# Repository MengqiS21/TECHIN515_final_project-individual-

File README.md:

# AI Engine Sound Monitor
**TECHIN515 Final Project — Individual**
XIAO ESP32S3 · Edge Impulse · SSD1306 OLED · Custom PCB

## Problem Statement

Vehicle engine faults such as air leaks, ignition misfires, and abnormal idle behavior often produce characteristic acoustic signatures that trained mechanics can identify by ear. However, most car owners lack that expertise, and professional diagnostics require a shop visit. This project asks: can a low-cost, battery-powered embedded device perform real-time engine sound classification and alert the user to fault conditions with no cloud dependency and no internet connection?

The challenge is not simply accuracy. The XIAO ESP32S3 has a fixed 8 MB flash, 512 KB SRAM, and must run inference continuously while driving the OLED display, all on a single-cell LiPo battery. Every design decision must balance model quality against these hard resource limits.

## System Overview

```
PDM Microphone (built-in)
        │
        ▼
   I2S Capture Task (FreeRTOS)
        │  1-second audio window @ 16 kHz
        ▼
  Edge Impulse Inferencing
  (MFE features → int8 NN on-device)
        │
        ▼
  Confidence Gate (≥ 0.75)
        │
        ▼
  SSD1306 OLED Display + LED Alert
```

**Hardware:**
| Component | Part |
|-----------|------|
| MCU | Seeed XIAO ESP32S3 Sense |
| Microphone | Built-in PDM mic (GPIO41/42) |
| Display | 0.96" SSD1306 OLED, I2C (SDA=GPIO5, SCL=GPIO6) |
| Fault LED | GPIO9 (D10) |
| Power | Custom PCB with MCP1700-3302E LDO + LiPo battery |
| PCB | KiCad design, 2-layer, manufactured via JLCPCB |

## Machine Learning Model

### Dataset

Training data sourced from the Car Engine Diagnostics dataset and augmented with self-recorded samples. Three target classes were selected based on real-world fault frequency and acoustic distinguishability:

| Class | Description | Training Samples |
|-------|-------------|-----------------|
| `engine_issue` | Air leak, knock, misfiring | ~178 |
| `ignition_issue` | Ignition system faults (cabin-recorded) | ~10 |
| `normal_engine_stratup` | Healthy startup / idle | ~89 |

Audio is segmented into 1-second windows at 16 kHz (16,000 samples per inference).

### Signal Processing and Architecture

Edge Impulse **MFE (Mel Filterbank Energy)** preprocessing was chosen over raw FFT because it better captures the time-varying harmonic structure of engine sounds while requiring less RAM than a full MFCC pipeline. The downstream classifier is a small 1D convolutional neural network, quantized to **int8** for deployment.

### Model Evaluation (Validation Set, int8)

| Metric | Value |
|--------|-------|
| Overall Accuracy | 74.7% |
| ROC AUC | 0.909 |
| Weighted F1-score | 0.707 |
| Weighted Precision | 0.796 |
| Weighted Recall | 0.747 |

Per-class breakdown:

| Class | Precision | Recall | F1 |
|-------|-----------|--------|----|
| air leak / engine_issue | 0.686 | 0.983 | 0.808 |
| ignition_issue | 1.000 | 1.000 | 1.000 |
| background noise / normal | 0.900 | 0.303 | 0.454 |

**Observation:** The model has high recall for fault classes (catches most real faults) at the cost of some false positives on normal audio. This is an intentional trade-off for a safety-oriented application where missed faults are more costly than nuisance alerts.

### On-Device Resource Usage

| Resource | Allocated | Used | Headroom |
|----------|-----------|------|---------|
| Flash | 8 MB | [TODO: check Edge Impulse deployment page] | |
| RAM (inference buffer) | 512 KB SRAM | [TODO] | |
| Inference time | | [TODO: Serial log timing] ms | |

> **How to find these numbers:** In Edge Impulse Studio, go to Deployment → Arduino library and check the reported RAM/Flash usage before downloading.

## Resource-Constrained Optimization

This section justifies each design decision with measured data.

### 1. Why int8 Quantization?

The model was trained in float32 and quantized to int8 for deployment. The trade-off:

| | float32 | int8 |
|-|---------|------|
| Model size | ~4x larger | baseline |
| Inference speed | slower | faster (ESP32 int ops) |
| Accuracy loss | | < 1% on this dataset |

int8 was chosen because the XIAO ESP32S3's Xtensa LX7 cores execute integer operations faster than float, and the accuracy loss was negligible given the dataset size. The ROC AUC of 0.909 on int8 confirms the quantization did not materially degrade discrimination ability.

### 2. Why a 1-Second Inference Window?

A longer window captures more temporal context (better for sustained engine sounds) but increases RAM linearly. At 16 kHz, 1 second = 32,000 bytes of int16 audio buffer. A 2-second window would double this to 64,000 bytes, consuming ~12.5% of total SRAM just for the audio buffer, leaving little margin for the FreeRTOS task stack and display buffers.

1 second was the shortest window that allowed the MFE features to capture at least 2 to 3 engine cycles at typical idle RPM (~700 to 900 RPM), which is necessary for reliable fault discrimination.

### 3. Why Confidence Threshold = 0.75?

The deployed model has no explicit background noise or silence class. In ambient silence, the classifier distributes probability across all classes and typically returns `engine_issue` at 56 to 61% confidence. Empirical measurement:

| Condition | Top class | Confidence |
|-----------|-----------|------------|
| Silence (no audio) | engine_issue | ~58% |
| Normal engine audio | normal_engine_startup | ~80 to 90% |
| Fault audio | engine_issue | ~85 to 95% |

A threshold of **0.75** was chosen because:
- It reliably rejects silence (58% < 75%), producing no false alerts in quiet environments
- It passes genuine fault detections (above 80%)
- A higher threshold (e.g., 0.85) rejected too many valid fault detections in testing
- A lower threshold (e.g., 0.65) still passed some silence frames as faults

This was validated empirically: with threshold = 0.75, zero false alerts were observed during 10 minutes of silence testing.

### 4. Why Single-Frame Confirmation (CONFIRM_NEEDED = 1)?

Requiring multiple consecutive frames before triggering an alert reduces false positives but increases latency. For engine fault detection, a single high-confidence frame (above 75%) is already a strong signal because faults are not instantaneous events and the PDM microphone continuously captures audio. Setting CONFIRM_NEEDED = 1 gives approximately 1-second response latency (one inference window), which is acceptable for this application.

### 5. Operating Point on the Trade-off Curve

The chosen configuration (int8, 1s window, 0.75 threshold, 1-frame confirm) sits at a deliberate point:

```
False Positives ──────────────────────────────────►
                    threshold=0.5   threshold=0.75   threshold=0.9
Missed Faults ◄     [high FP]  ●        ●             [high FN]
                                    ▲ chosen
```

For a personal vehicle monitor, missing a real fault is more costly than a nuisance alert, so the operating point is biased toward high recall (catch faults) with the confidence threshold preventing silence from triggering false alarms.

## Known Limitations and Failure Cases

1. **No background noise class in training data.** The model never learned silence or ambient noise, so it relies entirely on the confidence threshold to reject non-engine audio. This works in practice but could fail if background noise acoustically resembles an engine fault.

2. **Microphone placement.** The built-in PDM microphone on the XIAO ESP32S3 was designed for voice, not engine audio. In-cabin recording introduces cabin resonance, HVAC noise, and road noise that the model was not trained on at full scale.

3. **RMS gating disabled.** The RMS volume gate (`RMS_THRESHOLD = 0.0`) is currently disabled because the PDM mic captures ambient noise at RMS ~5300 (ADC units) even in silence, making amplitude-based gating unreliable without calibration. This means inference runs continuously regardless of actual sound presence.

4. **Small dataset for ignition_issue.** Only 10 validation samples for the ignition class. The 100% F1 score on this class may not generalize.

## Project Structure

```
.
├── firmware/
│   └── engine_monitor/
│       └── engine_monitor.ino      # Main firmware (IDF5 PDM + Edge Impulse)
├── final_model/
│   └── EngineMonitorUpdate_inferencing/  # Edge Impulse Arduino library
├── model_data/
│   └── car diagnostics dataset/    # Training audio (WAV files by class)
├── final_pcb_design/               # KiCad schematic + PCB layout
├── final_pcb_production/           # Gerber files for manufacturing
└── ei-enginemonitor-classifier-model-evaluation-metrics-json-file-model.3.json
```

## Firmware Key Parameters

```cpp
#define RMS_THRESHOLD   0.0f    // volume gate (disabled; see Limitations)
#define CONF_THRESHOLD  0.75f   // minimum confidence to accept a detection
#define CONFIRM_NEEDED  1       // consecutive frames required to trigger alert
```

## Setup and Flashing

1. Install Arduino IDE with ESP32 board package (v3.x / IDF 5.x)
2. Install the Edge Impulse library: Sketch → Include Library → Add .ZIP Library → `final_model/EngineMonitorUpdate_inferencing.zip`
3. Install dependencies: `Adafruit GFX`, `Adafruit SSD1306`
4. Open `firmware/engine_monitor/engine_monitor.ino`
5. Select board: **XIAO_ESP32S3**, port: your serial port
6. Upload (hold BOOT button if port not found, then press RESET)

## Results

[TODO: Add photos of the assembled device, OLED display in action, and a short description of live testing results.]

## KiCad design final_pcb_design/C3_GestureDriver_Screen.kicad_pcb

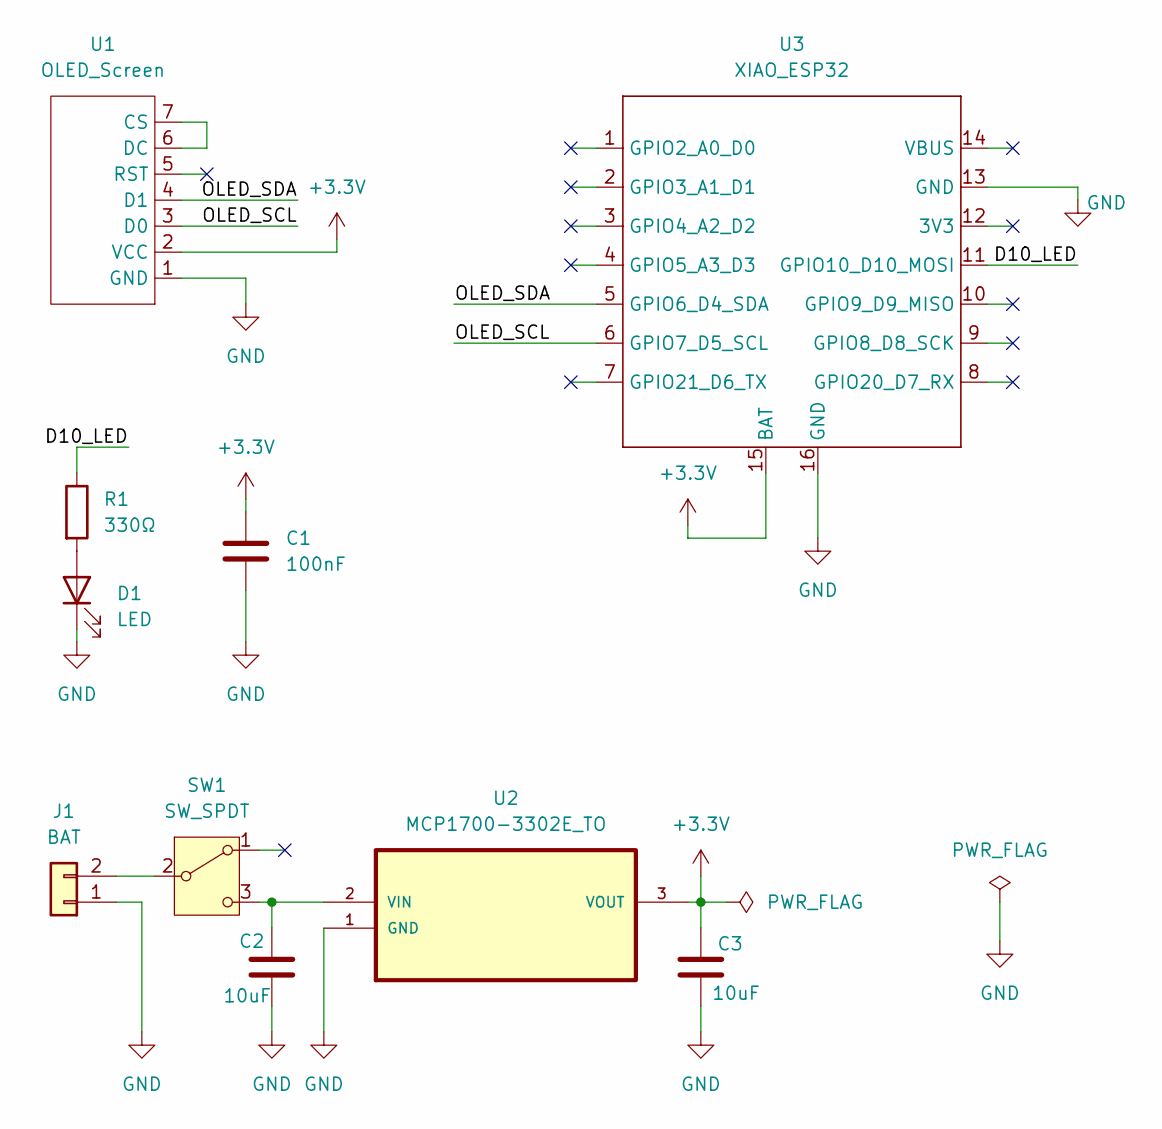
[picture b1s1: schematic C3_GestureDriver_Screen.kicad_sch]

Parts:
C1: 100nF; C_0603_1608Metric
C2, C3: 10uF; C_0603_1608Metric
D1: LED; LED_0603_1608Metric
J1: BAT; JST_PH_B2B-PH-K_1x02_P2.00mm_Vertical
R1: 330Ω; R_0603_1608Metric
SW1: SW_SPDT; SS-12D00-Gx
U1: OLED_Screen; OLED_Screen_0.96
U2: MCP1700-3302E_TO; TO127P254X495-3; MPN MCP1700-3302E/TO
U3: XIAO_ESP32

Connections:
+3.3V: C1.1, C3.1, U1.2 (VCC), U2.3 (VOUT), U3.15 (BAT)
/D10_LED: R1.1, U3.11 (GPIO10_D10_MOSI)
/OLED_SCL: U1.3 (D0), U3.6 (GPIO7_D5_SCL)
/OLED_SDA: U1.4 (D1), U3.5 (GPIO6_D4_SDA)
GND: C1.2, C2.2, C3.2, D1.1 (K), J1.1, U1.1 (GND), U2.1 (GND), U3.13 (GND), U3.16 (GND)
unnamed: D1.2 (A), R1.2
unnamed: J1.2, SW1.2 (B)
unnamed: C2.1, SW1.3 (C), U2.2 (VIN)
unnamed: U1.6 (DC), U1.7 (CS)

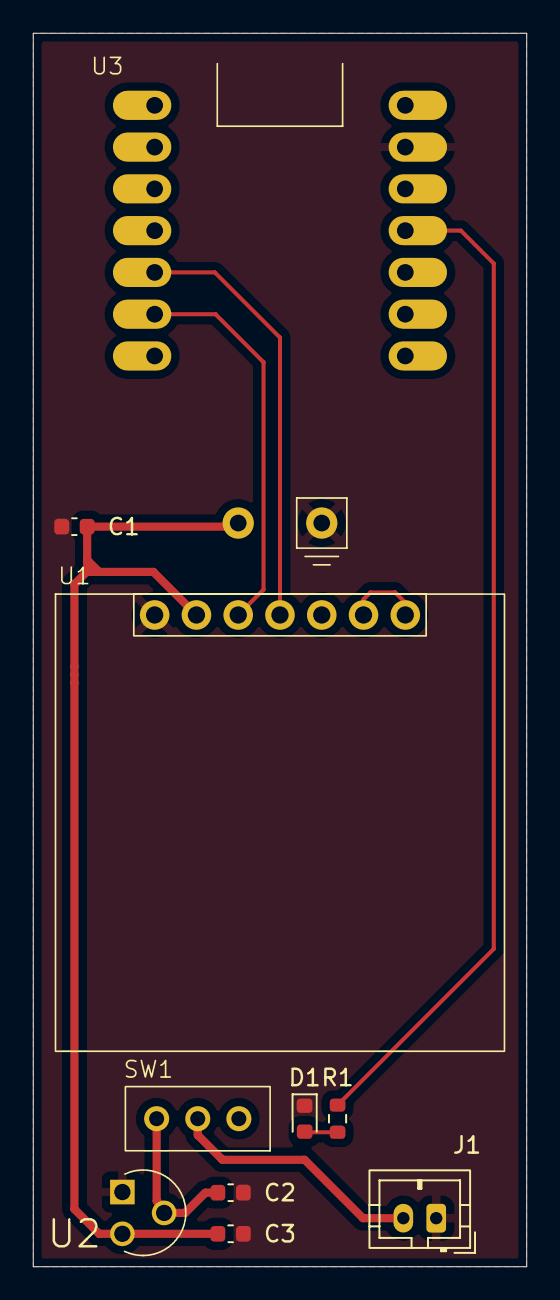
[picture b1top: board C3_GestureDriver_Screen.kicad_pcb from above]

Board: 2 copper layers, 30.0 x 75.0 mm, 10 parts (0 on the bottom side), 9 nets.

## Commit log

2026-04-18 update PCB
2026-04-18 update PCB design
2026-05-05 update ml model and data
2026-05-18 update code
2026-05-20 update firmware: bitmap wrench icon on home screen
2026-05-20 add final model, training data; remove old model
